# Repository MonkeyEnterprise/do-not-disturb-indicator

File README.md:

<!-- PROJECT LOGO -->
<div align="center">
    
<h3 align="center">00.25.0029 - Do Not Disturb Indicator</h3>
</div>
<!-- ABOUT THE PROJECT -->

### About The Project

---

This repository provides a comprehensive system to control an WS2812B LED using an ATTINY-85. It includes PCB files, 3D print files, firmware, and software for setting up and operating the system. The firmware implements a serial communication protocol for sending color and brightness commands to the WS2812B LED, using a packet structure with error-checking mechanisms. This setup allows for easy integration and customization of the do not disturb sign.

<!-- BUILD WITH -->
### Built With

* ![KiCad]
* ![VSCode]
* ![Visual Studio]
* ![SimulIDE]

<!-- LICENSE -->
### License

---
See `LICENSE` for more information.

<!-- MARKDOWN LINKS & IMAGES -->
<!-- https://www.markdownguide.org/basic-syntax/#reference-style-links -->
[KiCad]: https://img.shields.io/badge/KiCad-3F7D1F?style=for-the-badge&logoColor=white&labelColor=3F7D1F
[VSCode]: https://img.shields.io/badge/VSCode-007ACC?style=for-the-badge&logoColor=white&labelColor=007ACC
[Visual Studio]: https://img.shields.io/badge/Visual_Studio-5C2D91?style=for-the-badge&logoColor=white&labelColor=5C2D91
[SimulIDE]: https://img.shields.io/badge/SimulIDE-0094B3?style=for-the-badge&logoColor=white&labelColor=0094B3

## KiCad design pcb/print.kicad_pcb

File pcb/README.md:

# This directory is intended for the project pcb files

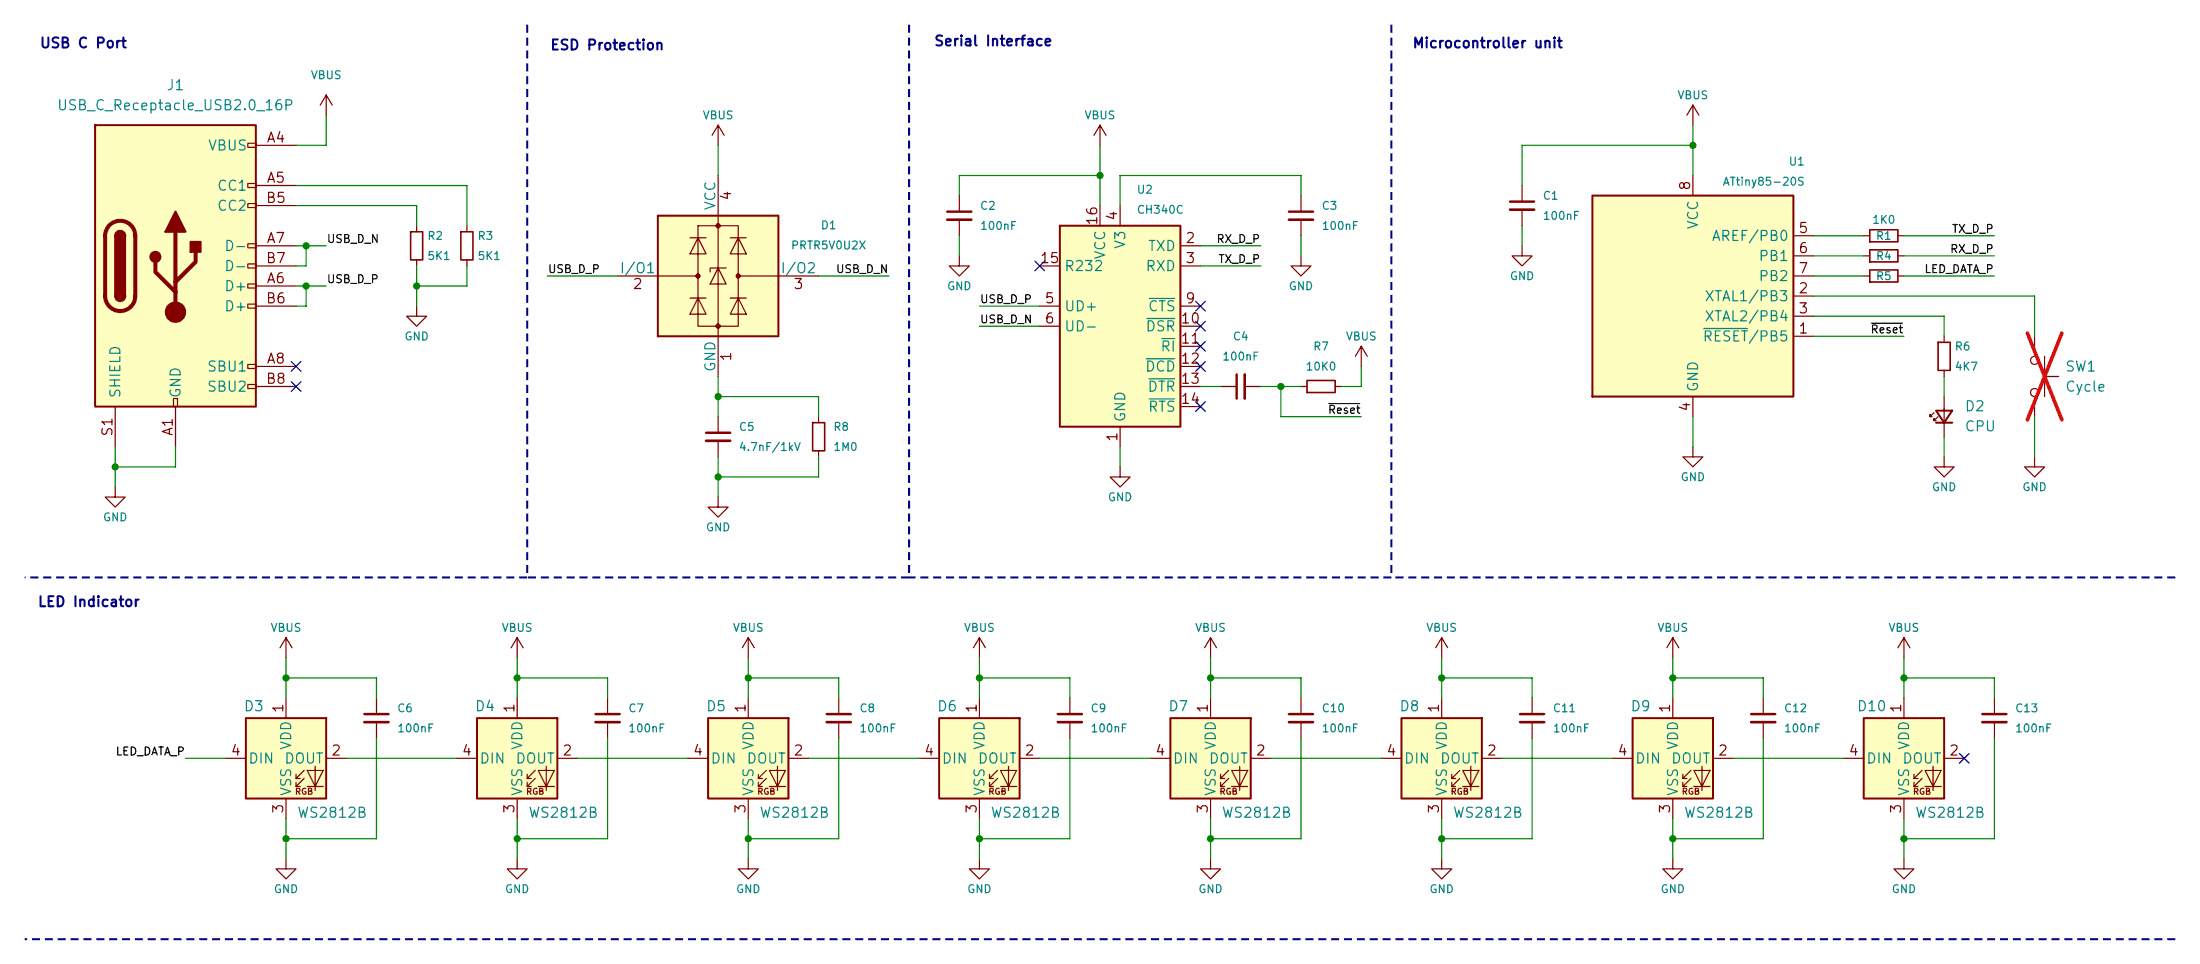
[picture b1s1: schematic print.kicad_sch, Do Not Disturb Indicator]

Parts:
C1, C2, C3, C4, C6, C7, C8, C9, C10, C11, C12, C13: 100nF; C_0402_1005Metric; LCSC C1525
C5: 4.7nF/1kV; C_0402_1005Metric; LCSC C1538
D1: PRTR5V0U2X; SOT-143; LCSC C12333
D2: CPU; D_0603_1608Metric; LCSC C2286
D3, D4, D5, D6, D7, D8, D9, D10: WS2812B; LED_WS2812B_PLCC4_5.0x5.0mm_P3.2mm; LCSC C2843785
J1: USB_C_Receptacle_USB2.0_16P; USB_C_Receptacle_GCT_USB4105-xx-A_16P_TopMnt_Horizontal; LCSC C2765186
R1, R4, R5: 1K0; R_0402_1005Metric; LCSC C25744
R2, R3: 5K1; R_0402_1005Metric; LCSC C25905
R6: 4K7; R_0402_1005Metric; LCSC C25900
R7: 10K0; R_0402_1005Metric; LCSC C25744
R8: 1M0; R_0402_1005Metric; LCSC C26083
SW1: Cycle; SW_PUSH_6mm_H4.3mm; not fitted
U1: ATtiny85-20S; SOIC-8_5.3x5.3mm_P1.27mm; LCSC C31540447
U2: CH340C; SOIC-16_3.9x9.9mm_P1.27mm; LCSC C84681

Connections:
/LED_DATA_P: D3.4 (DIN), R5.2
/RX_D_P: R4.2, U2.2 (TXD)
/TX_D_P: R1.2, U2.3 (RXD)
/USB_D_N: D1.3 (I/O2), J1.A7 (D-), J1.B7 (D-), U2.6 (UD-)
/USB_D_P: D1.2 (I/O1), J1.A6 (D+), J1.B6 (D+), U2.5 (UD+)
/~Reset: C4.2, R7.1, U1.1 (~RESET/PB5)
GND: C1.2, C2.2, C3.2, C5.2, C6.2, C7.2, C8.2, C9.2, C10.2, C11.2, C12.2, C13.2, D2.1 (K), D3.3 (VSS), D4.3 (VSS), D5.3 (VSS), D6.3 (VSS), D7.3 (VSS), D8.3 (VSS), D9.3 (VSS), D10.3 (VSS), J1.A1 (GND), J1.A12 (GND), J1.B1 (GND), J1.B12 (GND), J1.S1 (SHIELD), R2.2, R3.2, R8.2, SW1.2, U1.4 (GND), U2.1 (GND)
unnamed: C5.1, D1.1 (GND), R8.1
unnamed: D2.2 (A), R6.2
unnamed: D3.2 (DOUT), D4.4 (DIN)
unnamed: D4.2 (DOUT), D5.4 (DIN)
unnamed: D5.2 (DOUT), D6.4 (DIN)
unnamed: D6.2 (DOUT), D7.4 (DIN)
unnamed: D7.2 (DOUT), D8.4 (DIN)
unnamed: D8.2 (DOUT), D9.4 (DIN)
unnamed: D9.2 (DOUT), D10.4 (DIN)
unnamed: J1.A5 (CC1), R3.1
unnamed: J1.B5 (CC2), R2.1
unnamed: R1.1, U1.5 (AREF/PB0)
unnamed: R4.1, U1.6 (PB1)
unnamed: R5.1, U1.7 (PB2)
unnamed: SW1.1, U1.2 (XTAL1/PB3)
unnamed: R6.1, U1.3 (XTAL2/PB4)
unnamed: C3.1, U2.4 (V3)
unnamed: C4.1, U2.13 (~DTR)
VBUS: C1.1, C2.1, C6.1, C7.1, C8.1, C9.1, C10.1, C11.1, C12.1, C13.1, D1.4 (VCC), D3.1 (VDD), D4.1 (VDD), D5.1 (VDD), D6.1 (VDD), D7.1 (VDD), D8.1 (VDD), D9.1 (VDD), D10.1 (VDD), J1.A4 (VBUS), J1.A9 (VBUS), J1.B4 (VBUS), J1.B9 (VBUS), R7.2, U1.8 (VCC), U2.16 (VCC)

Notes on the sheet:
USB C Port
Microcontroller unit
Serial Interface
LED Indicator
ESD Protection

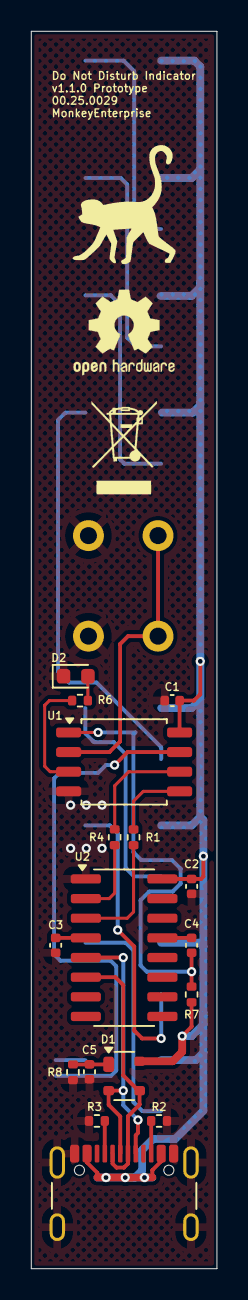
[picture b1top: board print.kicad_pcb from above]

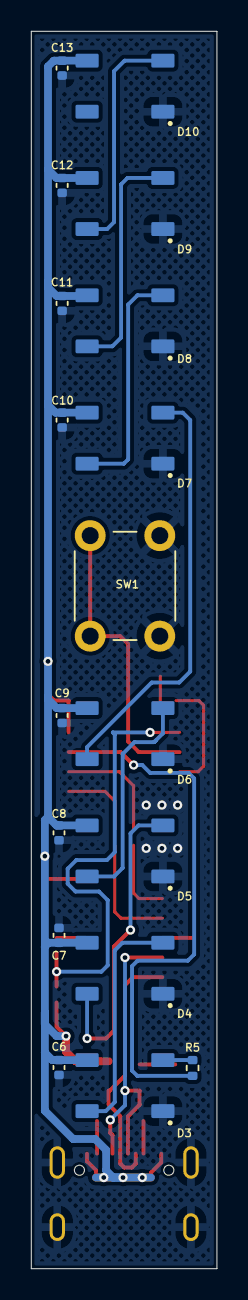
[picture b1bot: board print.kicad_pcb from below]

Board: 2 copper layers, 12.0 x 80.0 mm, 35 parts (18 on the bottom side), 26 nets.

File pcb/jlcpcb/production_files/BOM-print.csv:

Comment,Designator,Footprint,LCSC,Quantity
PRTR5V0U2X,D1,SOT-143,C12333,1
100nF,"C1,C10,C11,C12,C13,C2,C3,C4,C6,C7,C8,C9",C_0402_1005Metric,C1525,12
4.7nF/1kV,C5,C_0402_1005Metric,C1538,1
CPU,D2,D_0603_1608Metric,C2286,1
1K0,"R1,R4,R5,R7",R_0402_1005Metric,C25744,4
4K7,R6,R_0402_1005Metric,C25900,1
5K1,"R2,R3",R_0402_1005Metric,C25905,2
1M0,R8,R_0402_1005Metric,C26083,1
USB_C_Receptacle_USB2.0_16P,J1,USB_C_Receptacle_GCT_USB4105-xx-A_16P_TopMnt_Horizontal,C2765186,1
WS2812B,"D10,D3,D4,D5,D6,D7,D8,D9",LED_WS2812B_PLCC4_5.0x5.0mm_P3.2mm,C2843785,8
ATtiny85-20S,U1,SOIC-8_5.3x5.3mm_P1.27mm,C31540447,1
CH340C,U2,SOIC-16_3.9x9.9mm_P1.27mm,C84681,1

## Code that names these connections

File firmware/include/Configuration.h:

/**
 * @file Configuration.h
 * @brief Configuration header file for the device firmware.
 *
 * @copyright (c) 2025 Lorenzo Pouw, PouwerTronics/MonkeyEnterprise.
 * Licensed under the BSD license. This notice must remain in all redistributions.
 */

#ifndef __CONFIGURATION_H__
#define __CONFIGURATION_H__

#include <Arduino.h>
#include <Adafruit_NeoPixel.h>

// Define the CPU frequency for the AVR microcontroller
// ------- Hardware Configuration -------
#define TX_PIN PB0
#define RX_PIN PB1
#define LED_PIN PB2
#define CPU_PIN PB4
#define BUTTON_PIN PB3

// ------- Software Configuration -------
#define BAUD_RATE 9600
#define LED_COUNT 8
#define LED_TYPE NEO_GRB + NEO_KHZ800

// ------- Global Variables -------
struct GlobalVar
{
    uint8_t config_version;
    uint8_t mode;
    uint8_t red_mode0, green_mode0, blue_mode0, brightness_mode0;
    uint8_t red_mode1, green_mode1, blue_mode1, brightness_mode1;
    uint8_t red_mode2, green_mode2, blue_mode2, brightness_mode2;
};

const GlobalVar defaultCfg = {
    1,               // config_version
    0,               // mode
    255, 0, 0, 255,  // mode 0: red, green, blue, brightness
    0, 255, 0, 255,  // mode 1: red, green, blue, brightness
    255, 255, 0, 255 // mode 2: red, green, blue, brightness
};

#endif // __CONFIGURATION_H__

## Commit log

2025-05-26 Progress update
2025-05-26 First production update.
2025-05-27 Added the firmware.
2025-05-28 Revert changes from last commit.
2025-06-27 pcb v1.1.0 update
2025-07-11 Update config version, ignore .pyc, add log and settings
    Set config_version to 1 in Configuration.h and add '*.pyc' to .gitignore. Added main.log and settings.json files to software directory for application logging and configuration.
2025-10-01 Add 3D model files and update PCB project
    Added new 3D model files in .3mf, .stl, and .wrl formats for the project enclosure. Updated FreeCAD (.FCStd) and KiCad PCB project files to reflect changes related to the new model integration.
